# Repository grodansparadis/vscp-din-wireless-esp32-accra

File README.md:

# vscp-din-wireless-esp32-accra
Version 2 of Accra counter module.

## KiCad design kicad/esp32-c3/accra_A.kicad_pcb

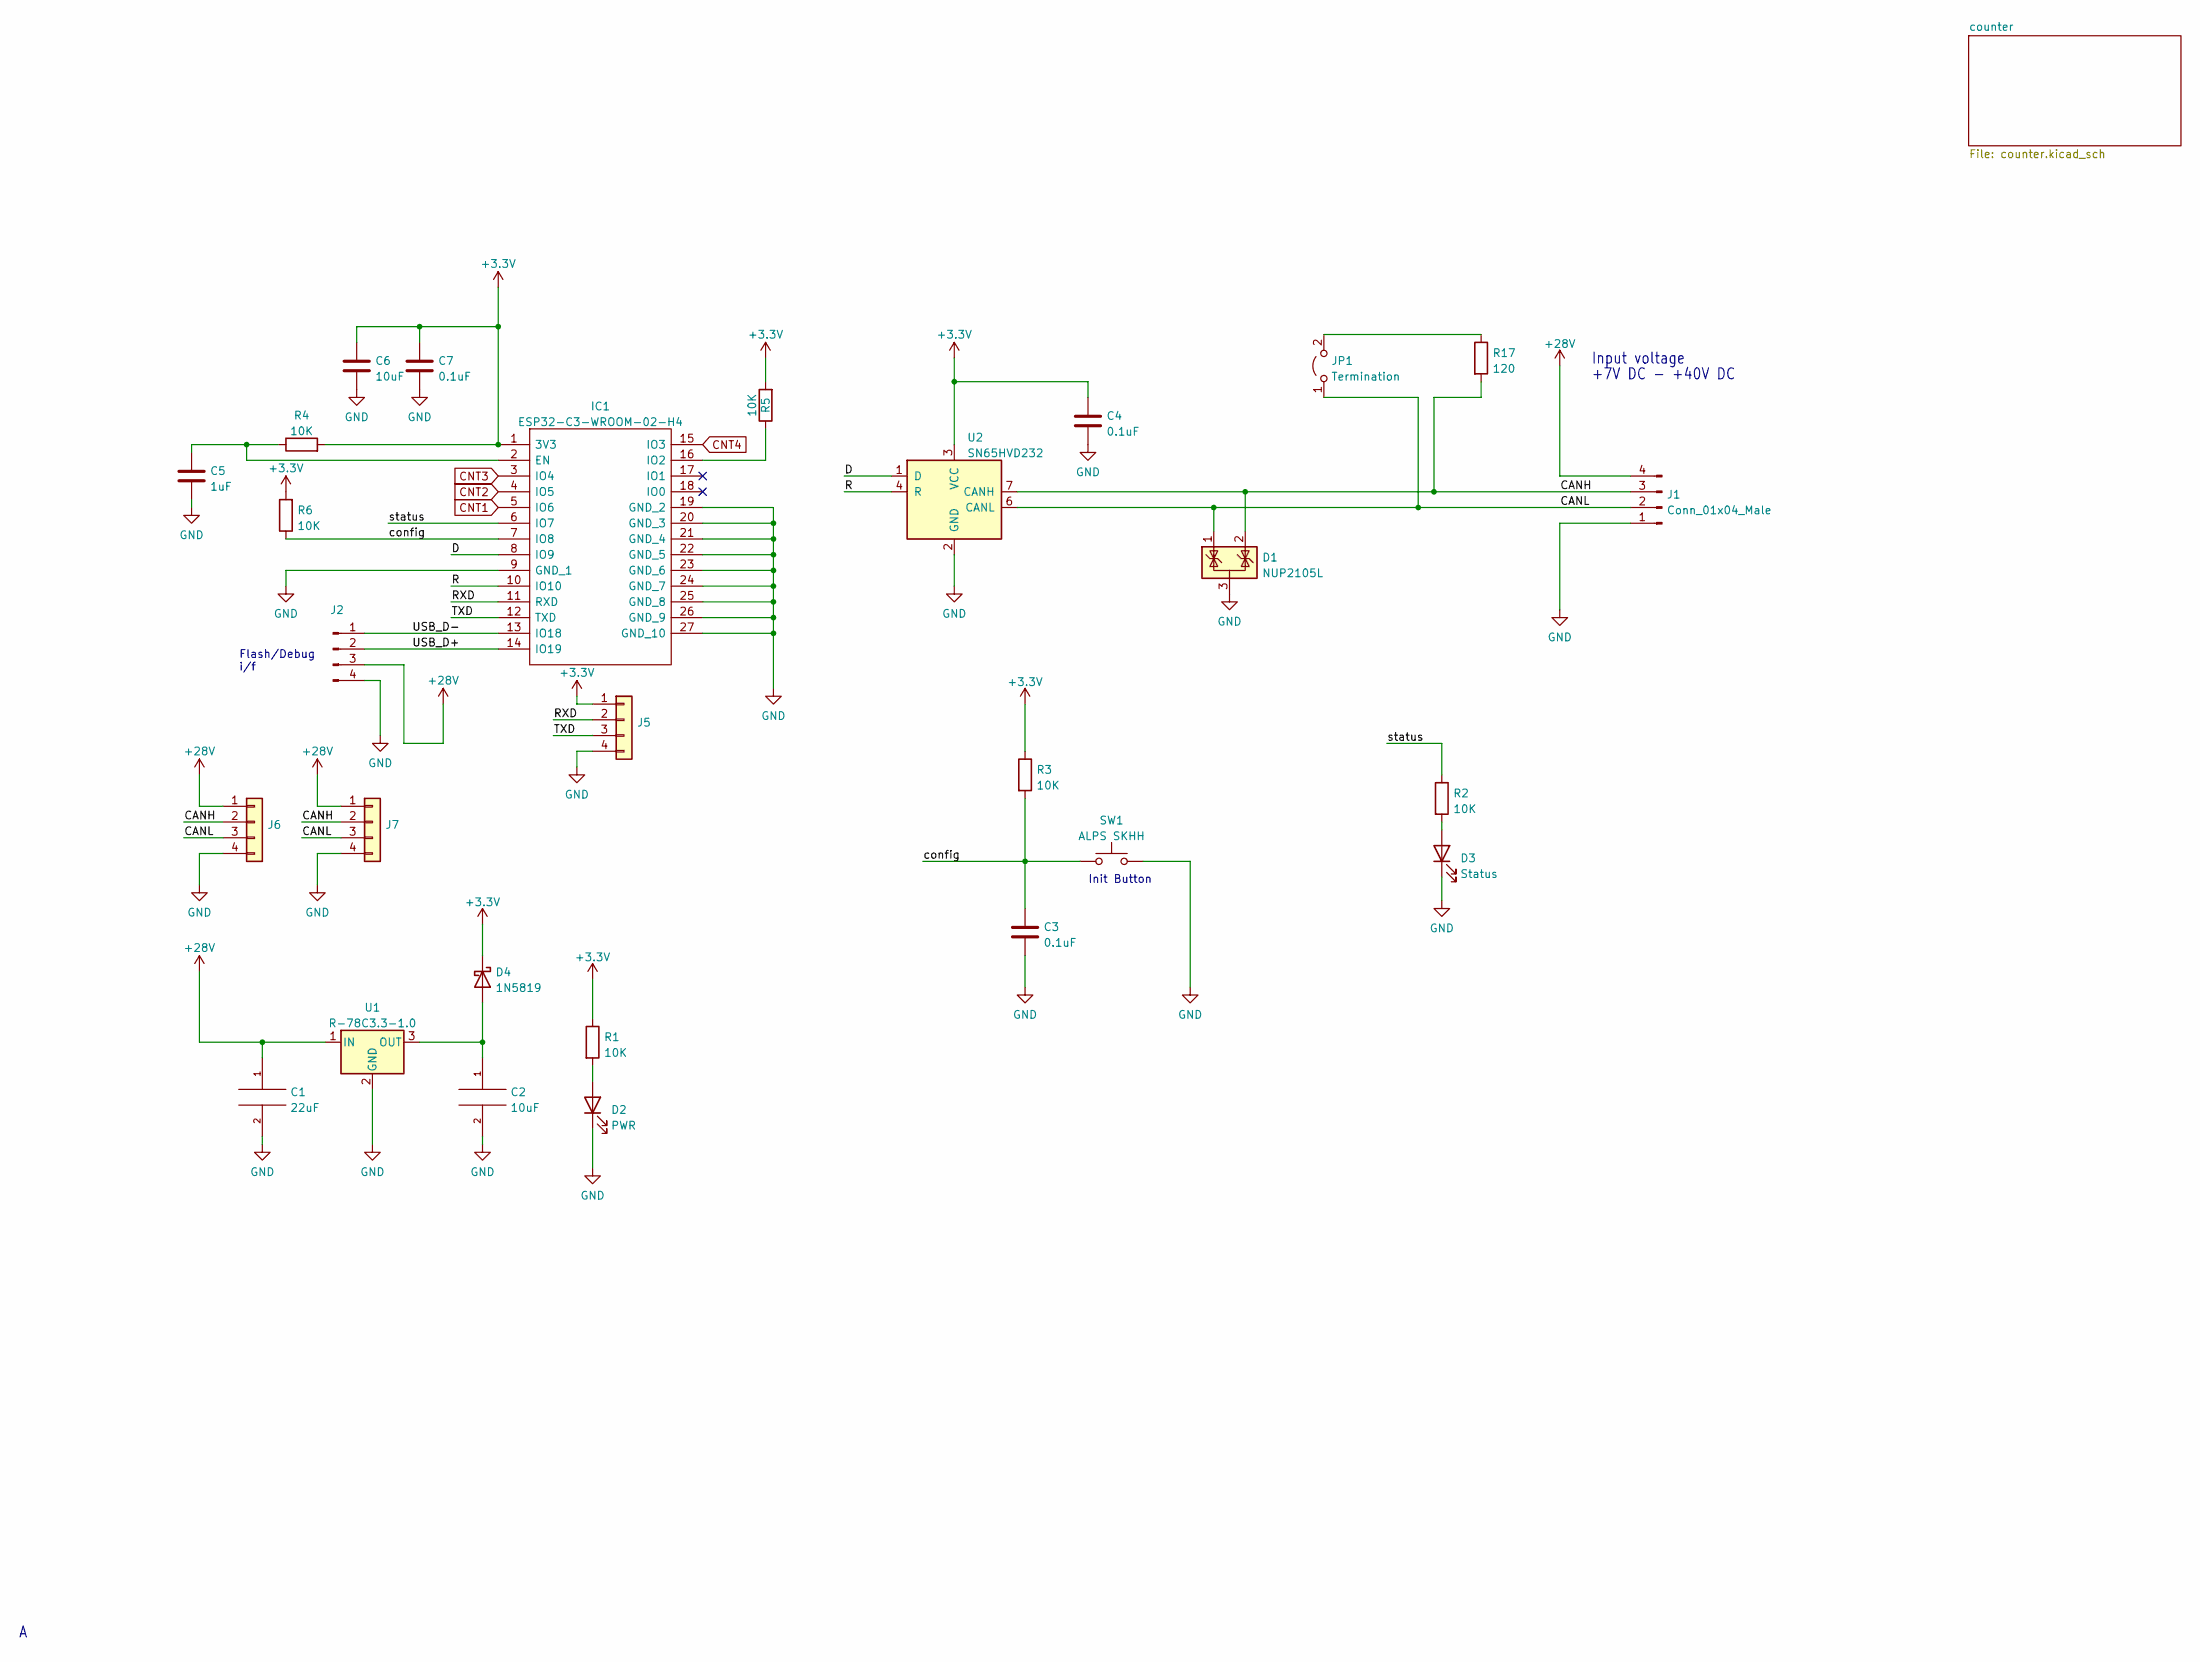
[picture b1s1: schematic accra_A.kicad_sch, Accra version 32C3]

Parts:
C1: 22uF; C_0805_2012Metric_Pad1.18x1.45mm_HandSolder
C2: 10uF; C_0805_2012Metric_Pad1.18x1.45mm_HandSolder
C3, C4, C7: 0.1uF; C_0805_2012Metric
C5: 1uF; C_0805_2012Metric
C6: 10uF; C_0805_2012Metric
D1: NUP2105L; SOT-23
D2: PWR; LED_0805_2012Metric
D3: Status; LED_0805_2012Metric
D4: 1N5819; D_SOD-123
IC1: ESP32-C3-WROOM-02-H4; ESP32C3WROOM02H4; Manufacturer_Part_Number ESP32-C3-WROOM-02-H4; Mouser Part Number 356-ESP32C3WROOM02H4
J1: Conn_01x04_Male; PhoenixContact_MCV_1,5_4-G-3.81_1x04_P3.81mm_Vertical
J2: Conn_01x04_Male; PinHeader_1x04_P2.54mm_Vertical
J5, J6, J7: Conn_01x04; Molex_KK-254_AE-6410-04A_1x04_P2.54mm_Vertical
JP1: Termination; PinHeader_1x02_P2.54mm_Vertical
R1, R2, R3, R4, R5, R6: 10K; R_0805_2012Metric
R17: 120; R_0805_2012Metric
SW1: ALPS SKHH; SW_Tactile_SPST_Angled_PTS645Vx31-2LFS
U1: R-78C3.3-1.0; Converter_DCDC_RECOM_R-78E-0.5_THT
U2: SN65HVD232; SOIC-8_3.9x4.9mm_P1.27mm

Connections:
+3V3: C4.1, C6.1, C7.1, D4.1 (K), IC1.1 (3V3), J5.1, R1.1, R3.1, R4.2, R5.2, R6.2, U2.3 (VCC); also elsewhere on the board
+28V: C1.1, J1.4, J2.3, J6.1, J7.1, U1.1 (IN)
/CANH: D1.2 (K), J1.3, J6.2, J7.2, R17.2, U2.7 (CANH)
/CANL: D1.1 (K), J1.2, J6.3, J7.3, JP1.1 (A), U2.6 (CANL)
/D: IC1.8 (IO9), U2.1 (D)
/R: IC1.10 (IO10), U2.4 (R)
/RXD: IC1.11 (RXD), J5.2
/TXD: IC1.12 (TXD), J5.3
/USB_D+: IC1.14 (IO19), J2.2
/USB_D-: IC1.13 (IO18), J2.1
/config: C3.1, IC1.7 (IO8), R3.2, R6.1, SW1.1
/status: IC1.6 (IO7), R2.1
CNT1: IC1.5 (IO6); also elsewhere on the board
CNT2: IC1.4 (IO5); also elsewhere on the board
CNT3: IC1.3 (IO4); also elsewhere on the board
CNT4: IC1.15 (IO3); also elsewhere on the board
GND: C1.2, C2.2, C3.2, C4.2, C5.2, C6.2, C7.2, D1.3 (A), D2.1 (K), D3.1 (K), IC1.9 (GND_1), IC1.19 (GND_2), IC1.20 (GND_3), IC1.21 (GND_4), IC1.22 (GND_5), IC1.23 (GND_6), IC1.24 (GND_7), IC1.25 (GND_8), IC1.26 (GND_9), IC1.27 (GND_10), J1.1, J2.4, J5.4, J6.4, J7.4, SW1.2, U1.2 (GND), U2.2 (GND); also elsewhere on the board
unnamed: C2.1, D4.2 (A), U1.3 (OUT)
unnamed: C5.1, IC1.2 (EN), R4.1
unnamed: D2.2 (A), R1.2
unnamed: D3.2 (A), R2.2
unnamed: IC1.16 (IO2), R5.1
unnamed: JP1.2 (B), R17.1

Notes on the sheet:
Init Button
Flash/Debug i/f
+7V DC - +40V DC
Input voltage

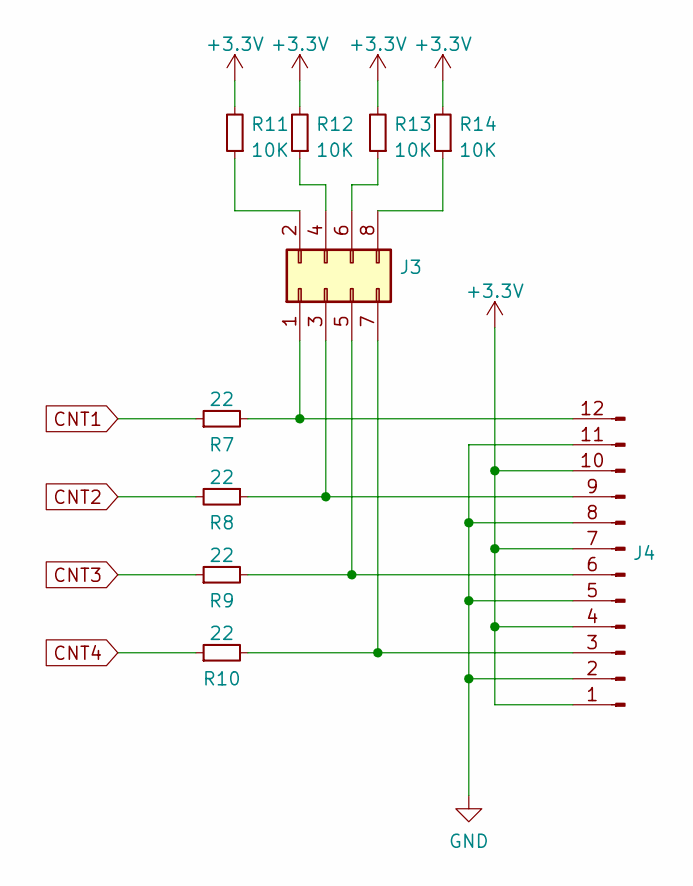
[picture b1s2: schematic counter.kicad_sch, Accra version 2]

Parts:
J3: Conn_02x04_Counter_Clockwise; PinHeader_2x04_P2.54mm_Vertical
J4: Conn_01x12_Male; PhoenixContact_MCV_1,5_12-G-3.5_1x12_P3.50mm_Vertical
R7, R8, R9, R10: 22; R_0805_2012Metric
R11, R12, R13, R14: 10K; R_0805_2012Metric

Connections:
+3V3: J4.1, J4.4, J4.7, J4.10, R11.2, R12.2, R13.2, R14.2; also elsewhere on the board
CNT1: R7.1; also elsewhere on the board
CNT2: R8.2; also elsewhere on the board
CNT3: R9.1; also elsewhere on the board
CNT4: R10.1; also elsewhere on the board
GND: J4.2, J4.5, J4.8, J4.11; also elsewhere on the board
unnamed: J3.1, J4.12, R7.2
unnamed: J3.2, R11.1
unnamed: J3.3, J4.9, R8.1
unnamed: J3.4, R12.1
unnamed: J3.5, J4.6, R9.2
unnamed: J3.6, R13.1
unnamed: J3.7, J4.3, R10.2
unnamed: J3.8, R14.1

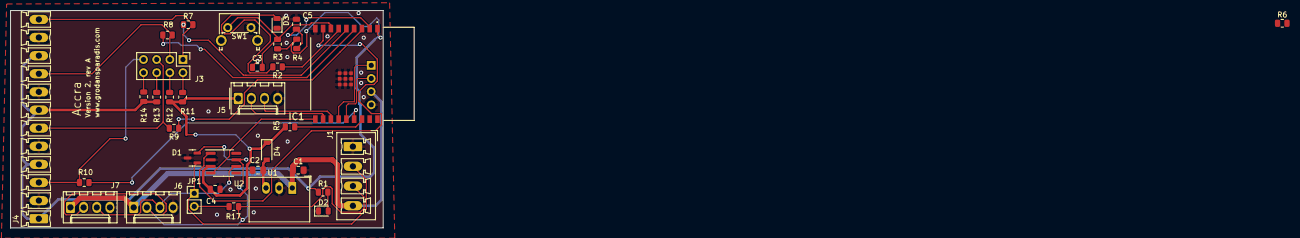
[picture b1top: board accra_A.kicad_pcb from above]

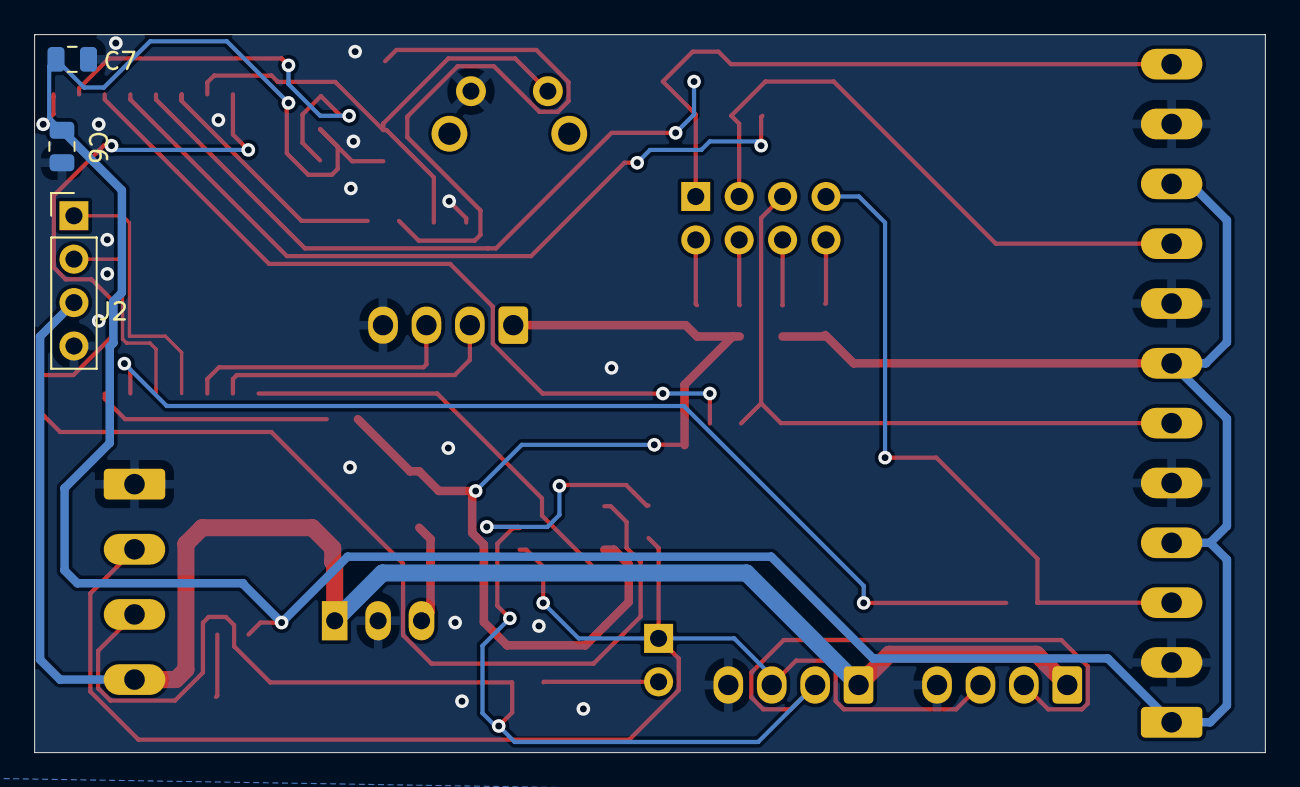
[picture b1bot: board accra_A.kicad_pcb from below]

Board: 6 copper layers, 72.0 x 42.0 mm, 38 parts (3 on the bottom side), 31 nets.

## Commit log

2022-06-15 Added board files
2022-06-16 Added CAN notes
2022-06-17 Added config standard link
2022-09-04 Added bom
2022-09-04 Removing unused files
2022-09-05 Removed some junk
2022-09-05 Changes power caps to SMD
2022-09-05 Added board to board connectors
2022-09-05 Added protection diod on input
2023-04-27 Closed open ground plane
2025-09-16 Removed backups from repository
2025-09-16 esp32 project removed, only C3 now
